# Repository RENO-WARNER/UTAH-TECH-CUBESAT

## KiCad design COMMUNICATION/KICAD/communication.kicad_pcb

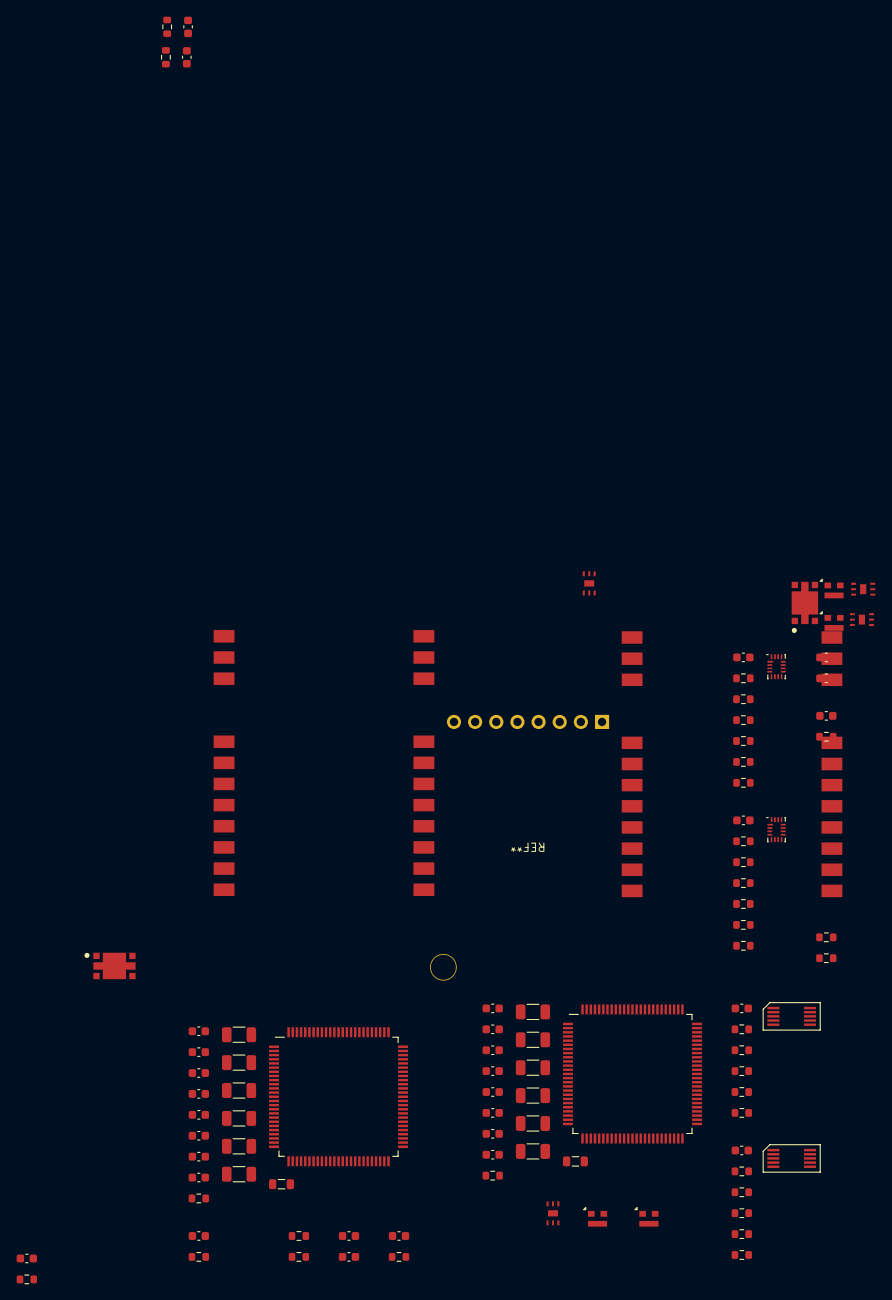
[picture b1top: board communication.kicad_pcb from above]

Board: 2 copper layers, 96 parts (0 on the bottom side), 57 nets, no tracks yet.

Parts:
C1, C19, C21, C22: 4.7nF; C_0603_1608Metric
C2, C3, C4, C7, C8, C9, C11, C12, C13, C14, C17, C20, C23, C24, C25, C28, C29, C30, C32, C33, C34, C35, C38, C40, C41, C42: 100nF; C_0603_1608Metric
C5, C10, C26, C31: 1uF; C_1206_3216Metric
C6, C18, C27, C39: 10uF; C_1206_3216Metric
C15, C16, C36, C37: 2.2uF; C_1206_3216Metric
L1, L2: 2.2uH; L_0805_2012Metric
R1, R2, R5, R12, R15, R16, R25, R26, R27, R28, R33, R34, R35, R36: 4.7kΩ; R_0603_1608Metric
R3, R4, R18, R19: 100kΩ; R_0603_1608Metric
R6, R7, R9, R10, R20, R21, R22, R23, R29, R30, R31, R32, R37, R38, R39, R40: 0Ω; R_0603_1608Metric
U1, U3, U10, U14: PAT1220-C-10DB; RF_Attenuator_Susumu_PAT1220
U2, U7: INA228
U4, U12: X4C09F1-30S
U6, U8, U13, U15: LMV221
U11, U16: E22-400M30S
U17, U21: STM32U5A5VJT6Q; STM32U5A5VJ
U18, U22: TCAL9538RSV

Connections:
/COMMUNICATION MODULE 1/ATTENUATOR1/IN: U1.1, U4.3 (REVERSE)
/COMMUNICATION MODULE 1/ATTENUATOR1/OUT: U1.2, U6.2 (RFIN)
/COMMUNICATION MODULE 1/ATTENUATOR2/IN: U3.1, U4.4 (FORWARD)
/COMMUNICATION MODULE 1/ATTENUATOR2/OUT: U3.2, U8.2 (RFIN)
/COMMUNICATION MODULE 1/COMMAND/CAN/V_3.3: C23.1, C24.1
/COMMUNICATION MODULE 1/COMMAND/EXPANDER/A0: R29.2, R30.1, U18.1 (A0)
/COMMUNICATION MODULE 1/COMMAND/EXPANDER/A1: R31.2, R32.1, U18.2 (A1)
/COMMUNICATION MODULE 1/COMMAND/EXPANDER/V_3.3: C20.1, R27.1, R28.1, R29.1, R31.1, U18.16 (VCC)
/COMMUNICATION MODULE 1/COMMAND/EXPANDER_INT: R28.2, U18.13 (INT)
/COMMUNICATION MODULE 1/COMMAND/EXPANDER_RESET: R27.2, U18.3 (RESET)
/COMMUNICATION MODULE 1/COMMAND/MCU/PH3: R26.1, U17.94 (PH3)
/COMMUNICATION MODULE 1/COMMAND/MCU/VDD11: C15.1, C16.1, L1.1, U17.49 (VDD11), U17.98 (VDD11)
/COMMUNICATION MODULE 1/COMMAND/MCU/VREF: C10.1, C12.1, U17.20 (VREF+)
/COMMUNICATION MODULE 1/COMMAND/MCU/V_3.3: C5.1, C6.1, C7.1, C8.1, C9.1, C11.1, C13.1, C14.1, C17.1, C18.1, U17.11 (VDD), U17.21 (VDDA), U17.27 (VDD), U17.47 (VDDSMPS), U17.51 (VDD), U17.73 (VDDUSB), U17.75 (VDD), U17.100 (VDD)
/COMMUNICATION MODULE 1/COMMAND/V_GND: C5.2, C6.2, C7.2, C8.2, C9.2, C10.2, C11.2, C12.2, C13.2, C14.2, C15.2, C16.2, C17.2, C18.2, C20.2, C23.2, C24.2, R26.2, R30.2, R32.2, U17.10 (VSS), U17.19 (VSSA), U17.26 (VSS), U17.48 (VSSSMPS), U17.50 (VSS), U17.74 (VSS), U17.99 (VSS), U18.8 (GND)
/COMMUNICATION MODULE 1/COUPLER/IN: U4.1 (IN), U11.21 (ANT)
/COMMUNICATION MODULE 1/DETECTOR1/OUT: C1.1, R3.1, U6.6 (OUT)
/COMMUNICATION MODULE 1/DETECTOR2/OUT: C19.1, R4.1, U8.6 (OUT)
/COMMUNICATION MODULE 1/DETECTOR_ENABLE: U6.4 (EN), U8.4 (EN)
/COMMUNICATION MODULE 1/MONITOR/A0: R6.2, R7.1, U2.2 (A0)
/COMMUNICATION MODULE 1/MONITOR/A1: R9.2, R10.1, U2.1 (A1)
/COMMUNICATION MODULE 1/MONITOR/ALERT: R5.2, U2.3 (ALERT)
/COMMUNICATION MODULE 1/MONITOR/IN: U2.8 (VBUS), U2.10 (IN+)
/COMMUNICATION MODULE 1/MONITOR/OUT: U2.9 (IN-), U11.9 (VCC), U11.10 (VCC)
/COMMUNICATION MODULE 1/MONITOR/V_3.3: C2.1, R5.1, R6.1, R9.1, U2.6 (VS)
/COMMUNICATION MODULE 1/MONITOR/V_GND: C2.2, R7.2, R10.2, U2.7 (GND)
/COMMUNICATION MODULE 2/ATTENUATOR1/IN: U12.3 (REVERSE), U14.1
/COMMUNICATION MODULE 2/ATTENUATOR1/OUT: U14.2, U15.2 (RFIN)
/COMMUNICATION MODULE 2/ATTENUATOR2/IN: U10.1, U12.4 (FORWARD)
/COMMUNICATION MODULE 2/ATTENUATOR2/OUT: U10.2, U13.2 (RFIN)
/COMMUNICATION MODULE 2/COMMAND/CAN/V_3.3: C41.1, C42.1
/COMMUNICATION MODULE 2/COMMAND/EXPANDER/A0: R37.2, R38.1, U22.1 (A0)
/COMMUNICATION MODULE 2/COMMAND/EXPANDER/A1: R39.2, R40.1, U22.2 (A1)
/COMMUNICATION MODULE 2/COMMAND/EXPANDER/V_3.3: C40.1, R35.1, R36.1, R37.1, R39.1, U22.16 (VCC)
/COMMUNICATION MODULE 2/COMMAND/EXPANDER_INT: R36.2, U22.13 (INT)
/COMMUNICATION MODULE 2/COMMAND/EXPANDER_RESET: R35.2, U22.3 (RESET)
/COMMUNICATION MODULE 2/COMMAND/MCU/PH3: R34.1, U21.94 (PH3)
/COMMUNICATION MODULE 2/COMMAND/MCU/VDD11: C36.1, C37.1, L2.1, U21.49 (VDD11), U21.98 (VDD11)
/COMMUNICATION MODULE 2/COMMAND/MCU/VREF: C31.1, C33.1, U21.20 (VREF+)
/COMMUNICATION MODULE 2/COMMAND/MCU/V_3.3: C26.1, C27.1, C28.1, C29.1, C30.1, C32.1, C34.1, C35.1, C38.1, C39.1, U21.11 (VDD), U21.21 (VDDA), U21.27 (VDD), U21.47 (VDDSMPS), U21.51 (VDD), U21.73 (VDDUSB), U21.75 (VDD), U21.100 (VDD)
/COMMUNICATION MODULE 2/COMMAND/V_GND: C26.2, C27.2, C28.2, C29.2, C30.2, C31.2, C32.2, C33.2, C34.2, C35.2, C36.2, C37.2, C38.2, C39.2, C40.2, C41.2, C42.2, R34.2, R38.2, R40.2, U21.10 (VSS), U21.19 (VSSA), U21.26 (VSS), U21.48 (VSSSMPS), U21.50 (VSS), U21.74 (VSS), U21.99 (VSS), U22.8 (GND)
/COMMUNICATION MODULE 2/COUPLER/IN: U12.1 (IN), U16.21 (ANT)
/COMMUNICATION MODULE 2/DETECTOR1/OUT: C22.1, R19.1, U15.6 (OUT)
/COMMUNICATION MODULE 2/DETECTOR2/OUT: C21.1, R18.1, U13.6 (OUT)
/COMMUNICATION MODULE 2/DETECTOR_ENABLE: U13.4 (EN), U15.4 (EN)
/COMMUNICATION MODULE 2/MONITOR/A0: R20.2, R21.1, U7.2 (A0)
/COMMUNICATION MODULE 2/MONITOR/A1: R22.2, R23.1, U7.1 (A1)
/COMMUNICATION MODULE 2/MONITOR/ALERT: R16.2, U7.3 (ALERT)
/COMMUNICATION MODULE 2/MONITOR/IN: U7.8 (VBUS), U7.10 (IN+)
/COMMUNICATION MODULE 2/MONITOR/OUT: U7.9 (IN-), U16.9 (VCC), U16.10 (VCC)
/COMMUNICATION MODULE 2/MONITOR/V_3.3: C3.1, R16.1, R20.1, R22.1, U7.6 (VS)
/COMMUNICATION MODULE 2/MONITOR/V_GND: C3.2, R21.2, R23.2, U7.7 (GND)
/CONNECTOR/I2C.SCL: U18.14 (SCL), U22.14 (SCL)
/CONNECTOR/I2C.SDA: U18.15 (SDA), U22.15 (SDA)
GND: C1.2, C19.2, C21.2, C22.2, R3.2, R4.2, R18.2, R19.2, U1.3, U3.3, U6.3 (GND), U6.DAP (GND), U8.3 (GND), U8.DAP (GND), U10.3, U11.1 (GND), U11.2 (GND), U11.3 (GND), U11.4 (GND), U11.5 (GND), U11.11 (GND), U11.12 (GND), U11.20 (GND), U11.22 (GND), U13.3 (GND), U13.DAP (GND), U14.3, U15.3 (GND), U15.DAP (GND), U16.1 (GND), U16.2 (GND), U16.3 (GND), U16.4 (GND), U16.5 (GND), U16.11 (GND), U16.12 (GND), U16.20 (GND), U16.22 (GND)
unnamed: L1.2, U17.46 (VLXSMPS)
unnamed: L2.2, U21.46 (VLXSMPS)

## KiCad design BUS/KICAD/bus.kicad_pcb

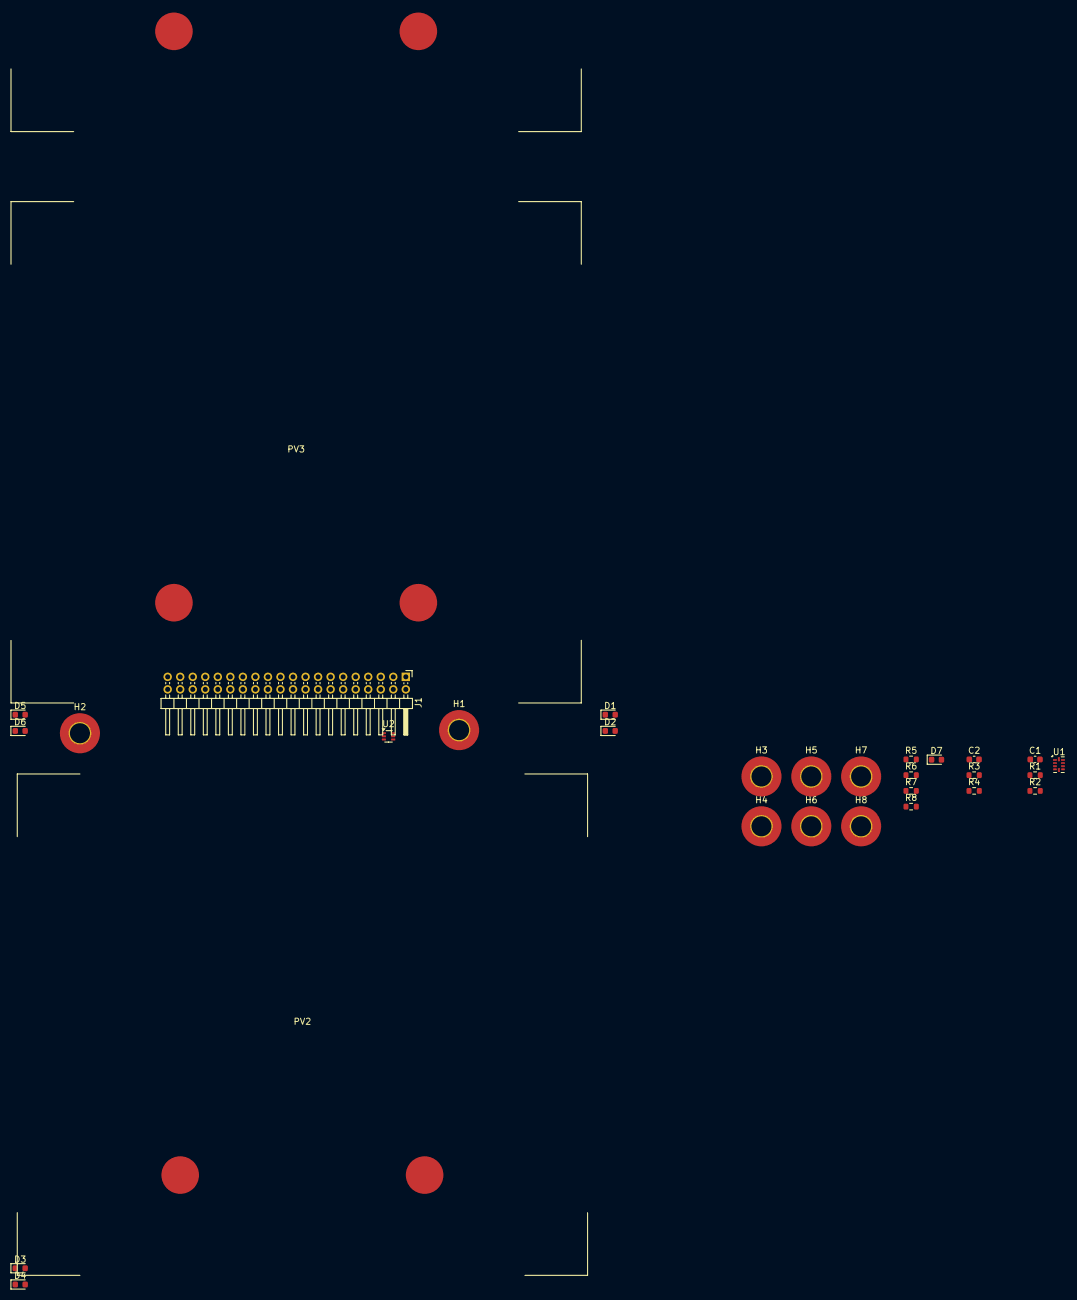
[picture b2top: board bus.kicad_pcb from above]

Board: 2 copper layers, 31 parts (0 on the bottom side), 22 nets, no tracks yet.

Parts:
C1: 100nF; C_0603_1608Metric
C2: 10nF; C_0603_1608Metric
D1, D3, D5: D_Zener; D_0603_1608Metric
D2, D4, D6: D_TVS; D_0603_1608Metric
D7: K857PE; D_0603_1608Metric
H1, H2, H3, H4, H5, H6, H7, H8: MountingHole_Pad; MountingHole_3.2mm_M3_Pad_TopBottom
J1: Conn_02x20_Odd_Even; PinHeader_2x20_P2.00mm_Horizontal
PV1, PV2, PV3: SM811K08TF
R1, R2, R3, R4: 0Ω; R_0603_1608Metric
R5, R6, R7, R8: 4.7kΩ; R_0603_1608Metric
U1: TLA2024; Texas_R-PQFP-N10
U2: TMP112N; Texas_R-PDSO-N6_DRL-6

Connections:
/ADC/AIN_1: R5.2, U1.5 (AIN1)
/ADC/AIN_2: R6.2, U1.6 (AIN2)
/ADC/AIN_3: R7.2, U1.7 (AIN3)
/CAN.H: J1.7, J1.8
/CAN.L: J1.9, J1.10
/I2C_A.SCL: J1.15, J1.16, U1.10 (SCL), U2.1 (SCL)
/I2C_A.SDA: J1.13, J1.14, U1.9 (SDA), U2.6 (SDA)
/I2C_B.SCL: J1.25, J1.26
/I2C_B.SDA: J1.27, J1.28
/MAGNET: J1.19, J1.20, J1.21, J1.22
/RESET: J1.29, J1.30
/SHUTDOWN: J1.11, J1.12
/SUN_SENSOR/PHOTODIODE_4: D7.1 (ANODE_4), R8.2
/USB.DM: J1.31, J1.32
/USB.DP: J1.33, J1.34
/V_3.3A: C1.1, C2.1, D7.2 (CATHODE), J1.17, J1.18, R1.1, R3.1, U1.8 (VDD), U2.5 (V+)
/V_3.3B: J1.23, J1.24
/V_BAT: J1.1, J1.2, J1.3, J1.4
/V_GND: C1.2, C2.2, D1.2 (A), D2.1 (A1), D3.2 (A), D4.1 (A1), D5.2 (A), D6.1 (A1), H1.1, H2.1, H3.1, H4.1, H5.1, H6.1, H7.1, H8.1, J1.5, J1.6, J1.35, J1.36, R2.2, R4.2, R5.1, R6.1, R7.1, R8.1, U1.3 (GND), U2.2 (GND), U2.3 (ALERT)
/V_SOLAR: D1.1 (K), D2.2 (A2), D3.1 (K), D4.2 (A2), D5.1 (K), D6.2 (A2), J1.37, J1.38, J1.39, J1.40
unnamed: R1.2, R2.1, U1.1 (ADDR)
unnamed: R3.2, R4.1, U2.4 (ADD0)

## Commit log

2024-08-19 docs: initialize
2024-08-20 fix: header
2024-08-20 fix: restructered template
2024-08-20 docs: added name/simpler function
2024-08-20 fix: added more text
2024-08-20 test: merging
2024-08-21 Resetted Command Function Report
2024-08-21 Added Design info
2024-08-21 Added Contents/Onshape
2024-08-21 Created Git Guide
2024-08-21 Improved Reports Guide
2024-08-21 Fixed Capitalization
2024-08-21 Removed Bold
2024-08-21 Created Template Reports
2024-08-21 Uploaded Screenshot for Git Guide
2024-08-21 Added General Info
2024-08-21 docs: added name
2024-08-21 Added Name
2024-08-21 Created Command function Report
2024-08-21 Created Power Function Report
2024-08-21 Add folder
2024-08-21 Create function.md
    made the function report, thank you
2024-08-21 Comms Updated Functions
2024-08-21 Detailed functions
2024-08-21 Created folder and function report
2024-08-22 Added Gitignore to prevent large build files
2024-08-22 Accidentally deleted gitignore
2024-08-22 Added Workflow to Upload to Dropbox
2024-08-23 Removed Signatures
2024-08-23 Added Clearer Message
2024-08-23 Created note page
2024-08-23 deleted line
2024-08-24 Updated Actuation Section
2024-08-26 Update notes.md
    Added Motor link
2024-08-26 Week 1 Progress Report
    very roughly done. will probably do most of what we said and more.
2024-08-26 Added Deadline Report
2024-09-06 names.md
    updated the names of the members and subsystem leader
2024-10-14 Added Datasheets / Application Notes
2024-10-14 Initialized BUS Kicad Project
2024-10-14 Initialized Command Kicad Project
2024-10-14 Initialized Control Kicad Project
2024-10-14 Initalized Basic Control Simulation
2024-10-14 Initialized Kicad Power Project
2024-10-14 Uploaded Test Images for Star Tracker
2024-10-14 Star Tracker Starter Code
2024-10-14 Initialized Communicaiton Kicad Project
2024-10-14 Added Transciever / Detector / Coupler Options
2024-10-14 EFuse / Ideal Diode Options
2024-10-14 Magnetorquer Optimization
2024-10-14 Added Connector Options along with protocols to use, outdated
2024-10-14 Moved Documentation
2024-10-14 General Design of Motor systems
2024-10-14 Create Kicad CubeSat Library
2024-10-14 Added More to gitignore for Kicad
2024-10-14 Created Rust Workspace for CubeSat
2024-10-14 Added Stakeholders
2024-10-14 Added General Requirements
2024-10-14 Added Sponsors
2024-10-14 Added More Info to Reports
2024-10-14 Added Header to Purchasing Reports
2024-10-22 Moved Datasheets and Added Datasheet
2024-10-22 Move Power Reports
2024-10-22 Added Motor Driver Datasheet
2024-10-22 Added Motor Driver Options
2024-10-22 Edited Schematics
2024-11-13 Add Plotter
2024-11-21 Add files via upload
    Deploy switch Option
2024-11-21 Create Battery Board
2024-11-23 Added Datasheets
2024-11-23 Added Prelimanary Orbital Calculations
2024-11-23 Updated Gitignore
2024-11-23 Moved Communication Kicad
2024-11-23 Removed unkown gender connector
2024-11-23 Updated Bus
2024-11-23 Initiated a loop based magnetorquer optimizer
2024-11-23 Added Batttery / MPPT design restraints
2024-11-23 Tuned Star Tracker
2024-11-23 Updated Control PCB / Schematics
2024-11-23 Updated Power Schematic / Kicad
2024-11-23 Updated Command Restraints(BOOT selection)
2024-11-23 Updated Command Kicad
2024-11-23 Updated Communication kicad
2024-11-23 Added Footprint requirements for Kicad
2024-11-23 Added General rating for components
2024-11-23 Decrepated Components
2024-11-23 Footprints that most likely will get deleted or modified.
2024-12-02 schematic design
